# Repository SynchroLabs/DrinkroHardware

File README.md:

#Introduction

This is a controller board with two L293D H-Bridge ICs used to run four DC
motors. In my application I used a 12VDC power supply and four 12VDC
peristaltic pumps for pumping drink ingredients.

The master branch of this repo may not be completely tested and ready to
produce. For a stable version, look at the release tags.

We are using this board in conjunction with a [Raspberry Pi 3 Model
B](https://www.raspberrypi.org/products/raspberry-pi-3-model-b/) and iOS,
Android, Windows Phone and Windows [drink
software](https://github.com/SynchroLabs/Drynkro) built with the [Synchro
platform](https://synchro.io).

#Hooking Things Up

The motors are hooked up to `J11`-`J14`. Plug in a DC power supply to `J1`.

Note that each motor can draw up to 300mA, so make sure that your DC power
supply can handle it if you want to drive more than one motor at a time.

Connect `J10` to a Raspberry Pi / Arduino / whatever you want as a controller.
Provide `VCCIO`, this must match your controller GPIO voltage, and connect
`GND`. `MOTOR1_EN` etc. are the motor enable lines, and can be PWM controlled
for speed control, or hooked up to regular GPIOs. I have not done a lot of
testing with speed control, I just turn the motors completely on and off with a
regular GPIO. The motor control lines have a pulldown resistor -- if these are
not installed, then the motor may default to enabled, depending on the L293D
chip you use. I'm using the ST Micro version and this was the case for that
chip.

`J2`-`J9` are used for motor direction. Each header has a VCCIO and a GND pin.
`DIR1` and `DIR2` must be set to opposite values -- that is, set `J2`
(`MOTOR1_DIR1`) to jumper to `VCCIO`, then set `J3` (`MOTOR1_DIR2`) to jumper
to `GND`. See the L293D datasheet for more information about how this works
internally in the chip. If the motor is running the wrong direction (pumping
the wrong way in my case), then swap both jumpers. If you want, you can skip
the jumpers and drive the direction pins directly from your controller.
However, there are no pullups or pulldowns on the lines, so be careful about
enabling a motor with the direction pins floating. I use jumpers in my case as
I don't care to run the pumps in reverse.

#Other Stuff

This is a good writeup on version control and EAGLE

https://spin.atomicobject.com/2015/01/19/hardware-version-control/

Some design considerations surround the current on VCC. Each motor can draw up
to 600mA, so the total current on VCC can be up to 2.4A (all four motors
running). Using the calculator at http://www.4pcb.com/trace-width-calculator.html
you need to make sure the trace width is suitable. The minimum trace for 2.4A
on 1oz copper is ~40mil.

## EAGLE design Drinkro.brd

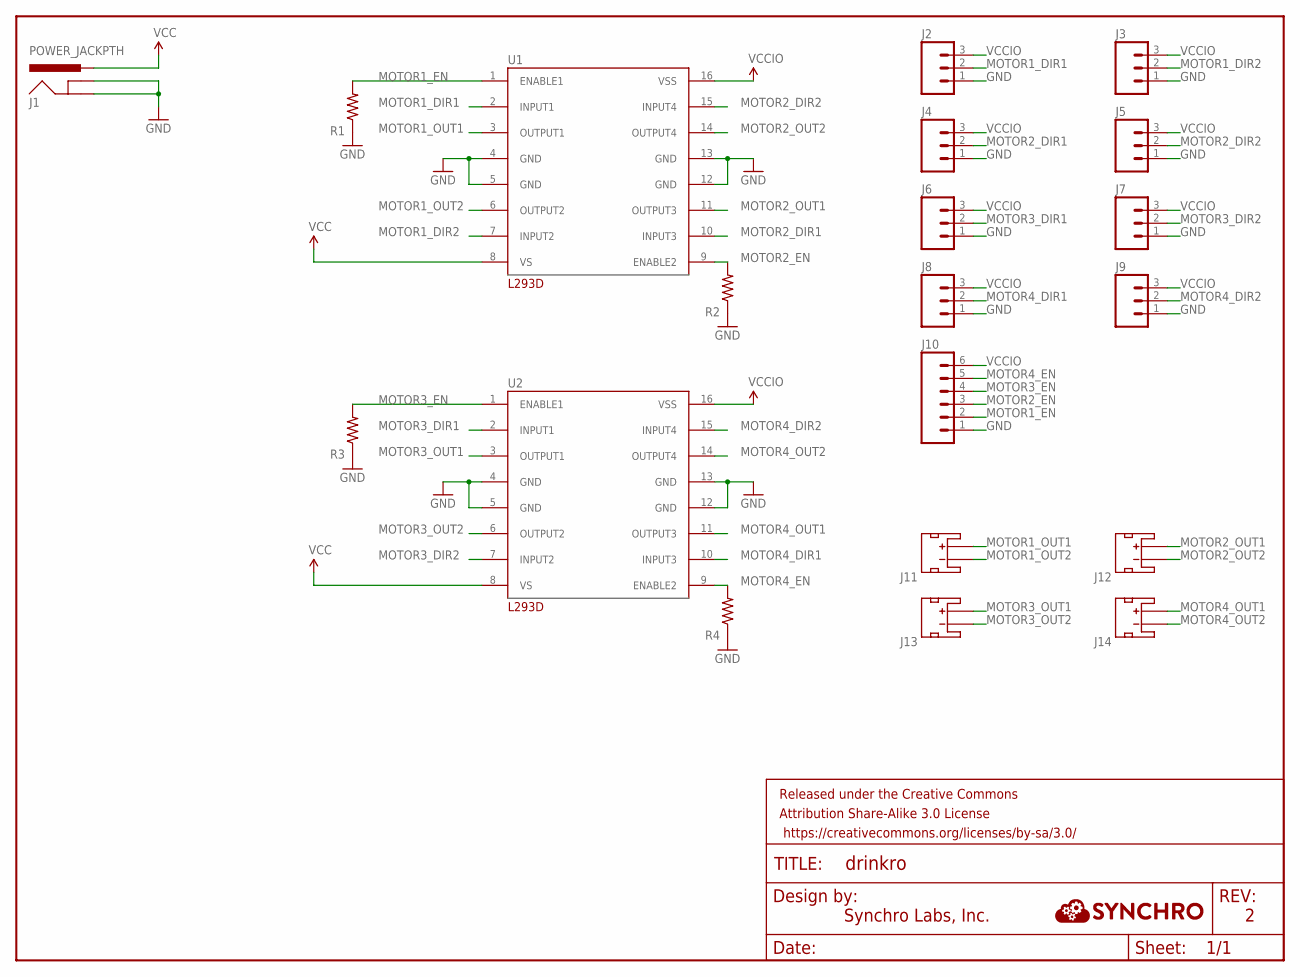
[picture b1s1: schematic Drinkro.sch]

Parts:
FRAME1: FRAME-LETTER; CREATIVE_COMMONS
J1: POWER_JACKPTH; POWER_JACK_PTH
J2, J3, J4, J5, J6, J7, J8, J9: M03PTH; 1X03
J10: M06SILK_FEMALE_PTH; 1X06
J11, J12, J13, J14: JST_2MM_MALE; JST-2-SMD
R1, R2, R3, R4: RESISTOR0805-RES; 0805
U1, U2: L293D; DIP

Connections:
GND: J1.GND, J1.GNDBREAK, J2.1, J3.1, J4.1, J5.1, J6.1, J7.1, J8.1, J9.1, J10.1, R1.1, R2.1, R3.1, R4.1, U1.4 (GND), U1.5 (GND), U1.12 (GND), U1.13 (GND), U2.4 (GND), U2.5 (GND), U2.12 (GND), U2.13 (GND)
MOTOR1_DIR1: J2.2, U1.2 (INPUT1)
MOTOR1_DIR2: J3.2, U1.7 (INPUT2)
MOTOR1_EN: J10.2, R1.2, U1.1 (ENABLE1)
MOTOR1_OUT1: J11.2 (+), U1.3 (OUTPUT1)
MOTOR1_OUT2: J11.1 (-), U1.6 (OUTPUT2)
MOTOR2_DIR1: J4.2, U1.10 (INPUT3)
MOTOR2_DIR2: J5.2, U1.15 (INPUT4)
MOTOR2_EN: J10.3, R2.2, U1.9 (ENABLE2)
MOTOR2_OUT1: J12.2 (+), U1.11 (OUTPUT3)
MOTOR2_OUT2: J12.1 (-), U1.14 (OUTPUT4)
MOTOR3_DIR1: J6.2, U2.2 (INPUT1)
MOTOR3_DIR2: J7.2, U2.7 (INPUT2)
MOTOR3_EN: J10.4, R3.2, U2.1 (ENABLE1)
MOTOR3_OUT1: J13.2 (+), U2.3 (OUTPUT1)
MOTOR3_OUT2: J13.1 (-), U2.6 (OUTPUT2)
MOTOR4_DIR1: J8.2, U2.10 (INPUT3)
MOTOR4_DIR2: J9.2, U2.15 (INPUT4)
MOTOR4_EN: J10.5, R4.2, U2.9 (ENABLE2)
MOTOR4_OUT1: J14.2 (+), U2.11 (OUTPUT3)
MOTOR4_OUT2: J14.1 (-), U2.14 (OUTPUT4)
VCC: J1.PWR, U1.8 (VS), U2.8 (VS)
VCCIO: J2.3, J3.3, J4.3, J5.3, J6.3, J7.3, J8.3, J9.3, J10.6, U1.16 (VSS), U2.16 (VSS)

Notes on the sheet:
Synchro Labs, Inc.

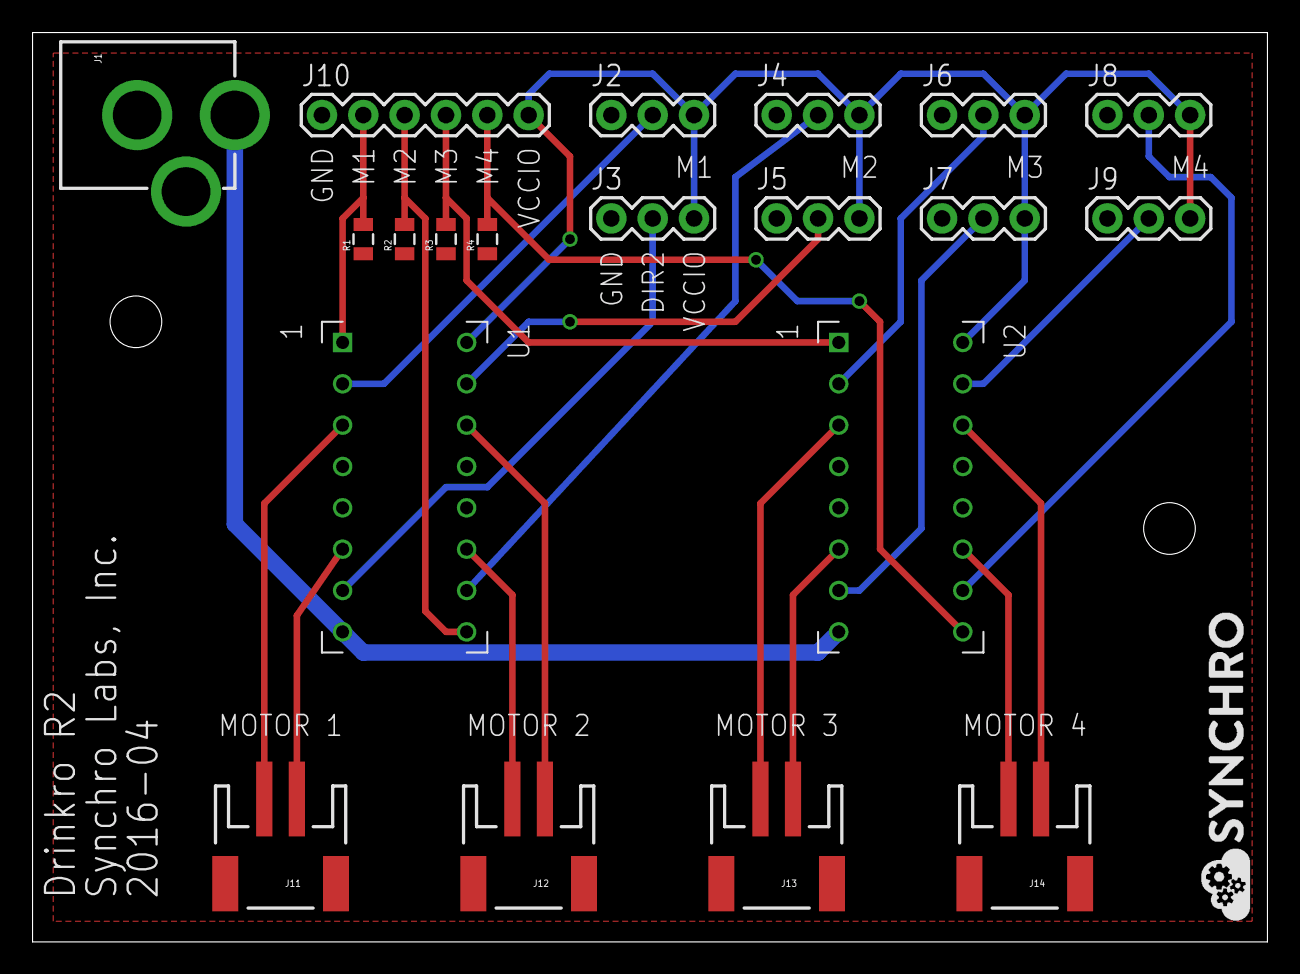
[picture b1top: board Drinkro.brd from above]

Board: 2 copper layers, 75.9 x 55.9 mm, 21 parts (0 on the bottom side), 23 nets.

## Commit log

2016-05-01 R1 final board.
2016-05-01 Forgot the LBR.
2016-05-01 First cut of .gitignore.
2016-05-01 Added eagle.epf to .gitignore.
2016-05-01 Added revision and company.
2016-05-01 Added README.md.
2016-05-02 Silkscreen changes. Revision bump to 2.
2016-05-02 Increased wire width on VCC and added mounting holes.
2016-05-04 Added logo.
2016-05-04 Cleaned up MOTOR1_OUT1 routing.
2016-05-04 Added logo to schematic.
2016-05-08 Added ST L293D datasheet.
2016-05-17 More bitmap futzing. Not sure where this all ends up.
2016-05-20 Changed mounting hole size.
2016-05-21 More futzing with the bitmap.
2016-07-20 README work.
2016-12-14 Fixed some text alignment, new Eagle version.

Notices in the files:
parts and their libraries:
SparkFun-Retired: Licensing:Creative Commons ShareAlike 4.0 International - https://creativecommons.org/licenses/by-sa/4.0
SparkFun-Retired: Released under the Creative Commons Attribution Share-Alike 3.0 License
SparkFun-Retired: https://creativecommons.org/licenses/by-sa/3.0
